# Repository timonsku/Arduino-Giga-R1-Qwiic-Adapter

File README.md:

# Arduino Giga R1 Qwiic Adapter

A small adapter for adding a I2C Qwiic / Stemma QT connector (footprint for both right angle and vertical) to the front 2x10 pin connector of the Arduino Giga R1.

BOM:

SMT 2x2 header: Molex 15-91-0040 or equivalent

Qwiic: JST-SH 4 pin or Amphenol 10116782-004010LF

2x 0603 resistors depending on your needs. 2.2k-10kohm is typical.

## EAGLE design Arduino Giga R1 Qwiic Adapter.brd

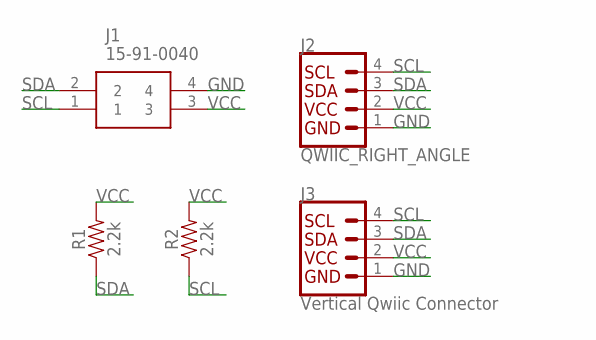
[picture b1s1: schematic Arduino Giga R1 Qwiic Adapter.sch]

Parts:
J1: 15-91-0040; 15910040
J2: QWIIC_RIGHT_ANGLE; JST04_1MM_RA
J3: Vertical Qwiic Connector; JST04_1MM_VERT
R1, R2: 2.2k; 0603

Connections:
GND: J1.4, J2.1, J3.1
SCL: J1.1, J2.4, J3.4, R2.1
SDA: J1.2, J2.3, J3.3, R1.1
VCC: J1.3, J2.2, J3.2, R1.2, R2.2

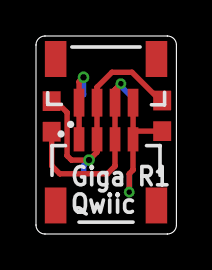
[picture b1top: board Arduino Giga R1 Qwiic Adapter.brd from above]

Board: 2 copper layers, 7.8 x 11.0 mm, 5 parts (1 on the bottom side), 4 nets.

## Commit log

2023-03-19 rename gerber zip
2023-03-19 add parts info

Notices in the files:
parts and their libraries:
SparkFun-Connectors: Licensing: Creative Commons ShareAlike 4.0 International - https://creativecommons.org/licenses/by-sa/4.0
